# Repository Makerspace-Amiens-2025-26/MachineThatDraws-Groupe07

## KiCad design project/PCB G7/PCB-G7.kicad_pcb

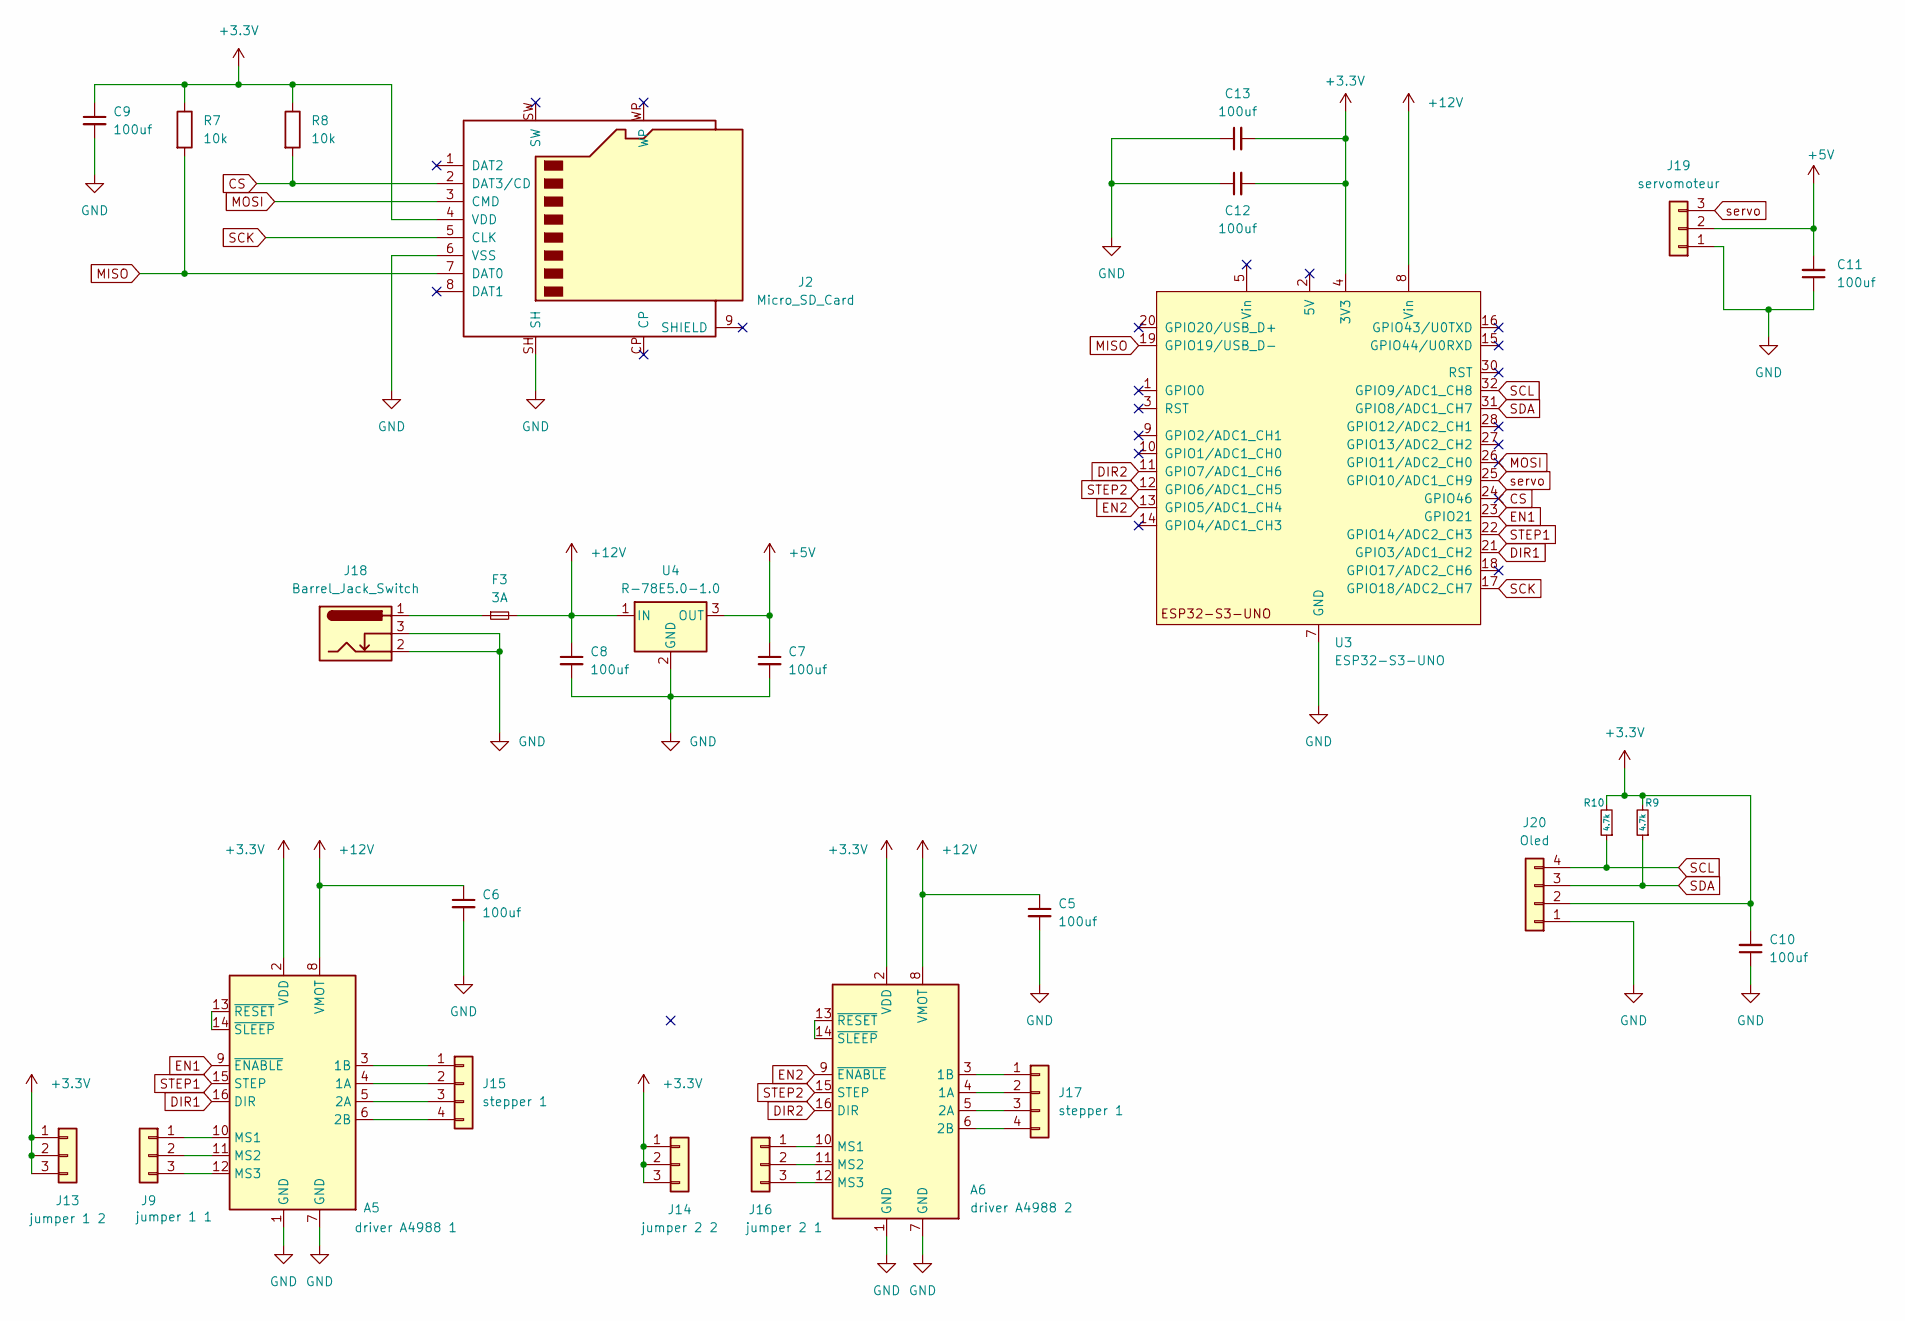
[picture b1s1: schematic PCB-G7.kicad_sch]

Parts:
A5: driver A4988 1; Pololu_Breakout-16_15.2x20.3mm
A6: driver A4988 2; Pololu_Breakout-16_15.2x20.3mm
C5, C6: 100uf; C_Radial_D8.0mm_H11.5mm_P3.50mm
C7, C8: 100uf; C_1206_3216Metric_Pad1.33x1.80mm_HandSolder
C9, C10, C12, C13: 100uf; C_1206
C11: 100uf; C_1206_3216Metric
F3: 3A; Fuseholder_Blade_Mini_Keystone_3568
J2: Micro_SD_Card; SD_Hirose_DM1AA_SF_PEJ82
J9: jumper 1 1; PinHeader_1x03_P2.54mm_Vertical
J13: jumper 1 2; PinHeader_1x03_P2.54mm_Vertical
J14: jumper 2 2; PinHeader_1x03_P2.54mm_Vertical
J15, J17: stepper 1; PinHeader_1x04_P2.54mm_Vertical
J16: jumper 2 1; PinHeader_1x03_P2.54mm_Vertical
J18: Barrel_Jack_Switch; BarrelJack_Horizontal
J19: servomoteur; PinHeader_1x03_P2.54mm_Vertical
J20: Oled; PinHeader_1x04_P2.54mm_Vertical
R7, R8: 10k; R_1206
R9, R10: 4.7k; R_1206
U3: ESP32-S3-UNO; ESP_S3_UNO
U4: R-78E5.0-1.0; Converter_DCDC_RECOM_R-78E-0.5_THT

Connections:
+3.3V: A5.2 (VDD), A6.2 (VDD), C9.1, C10.2, C12.2, C13.2, J2.4 (VDD), J13.1, J13.2, J13.3, J14.1, J14.2, J14.3, J20.2, R7.1, R8.1, R9.2, R10.2, U3.4 (3V3)
+5V: C7.1, C11.2, J19.2, U4.3 (OUT)
+12V: A5.8 (VMOT), A6.8 (VMOT), C5.1, C6.1, C8.1, F3.2, U3.8 (Vin), U4.1 (IN)
CS: J2.2 (DAT3/CD), R8.2, U3.24 (GPIO46)
DIR1: A5.16 (DIR), U3.21 (GPIO3/ADC1_CH2)
DIR2: A6.16 (DIR), U3.11 (GPIO7/ADC1_CH6)
EN1: A5.9 (~ENABLE), U3.23 (GPIO21)
EN2: A6.9 (~ENABLE), U3.13 (GPIO5/ADC1_CH4)
GND: A5.1 (GND), A5.7 (GND), A6.1 (GND), A6.7 (GND), C5.2, C6.2, C7.2, C8.2, C9.2, C10.1, C11.1, C12.1, C13.1, J2.6 (VSS), J2.SH, J18.2, J18.3, J19.1, J20.1, U3.6 (GND), U3.7 (GND), U3.29 (GND), U4.2 (GND)
MISO: J2.7 (DAT0), R7.2, U3.19 (GPIO19/USB_D-)
MOSI: J2.3 (CMD), U3.26 (GPIO11/ADC2_CH0)
unnamed: A5.4 (1A), J15.2
unnamed: A5.3 (1B), J15.1
unnamed: A5.5 (2A), J15.3
unnamed: A5.6 (2B), J15.4
unnamed: A5.10 (MS1), J9.1
unnamed: A5.11 (MS2), J9.2
unnamed: A5.12 (MS3), J9.3
unnamed: A5.13 (~RESET), A5.14 (~SLEEP)
unnamed: A6.4 (1A), J17.2
unnamed: A6.3 (1B), J17.1
unnamed: A6.5 (2A), J17.3
unnamed: A6.6 (2B), J17.4
unnamed: A6.10 (MS1), J16.1
unnamed: A6.11 (MS2), J16.2
unnamed: A6.12 (MS3), J16.3
unnamed: A6.13 (~RESET), A6.14 (~SLEEP)
unnamed: F3.1, J18.1
SCK: J2.5 (CLK), U3.17 (GPIO18/ADC2_CH7)
SCL: J20.4, R10.1, U3.32 (GPIO9/ADC1_CH8)
SDA: J20.3, R9.1, U3.31 (GPIO8/ADC1_CH7)
STEP1: A5.15 (STEP), U3.22 (GPIO14/ADC2_CH3)
STEP2: A6.15 (STEP), U3.12 (GPIO6/ADC1_CH5)
servo: J19.3, U3.25 (GPIO10/ADC1_CH9)

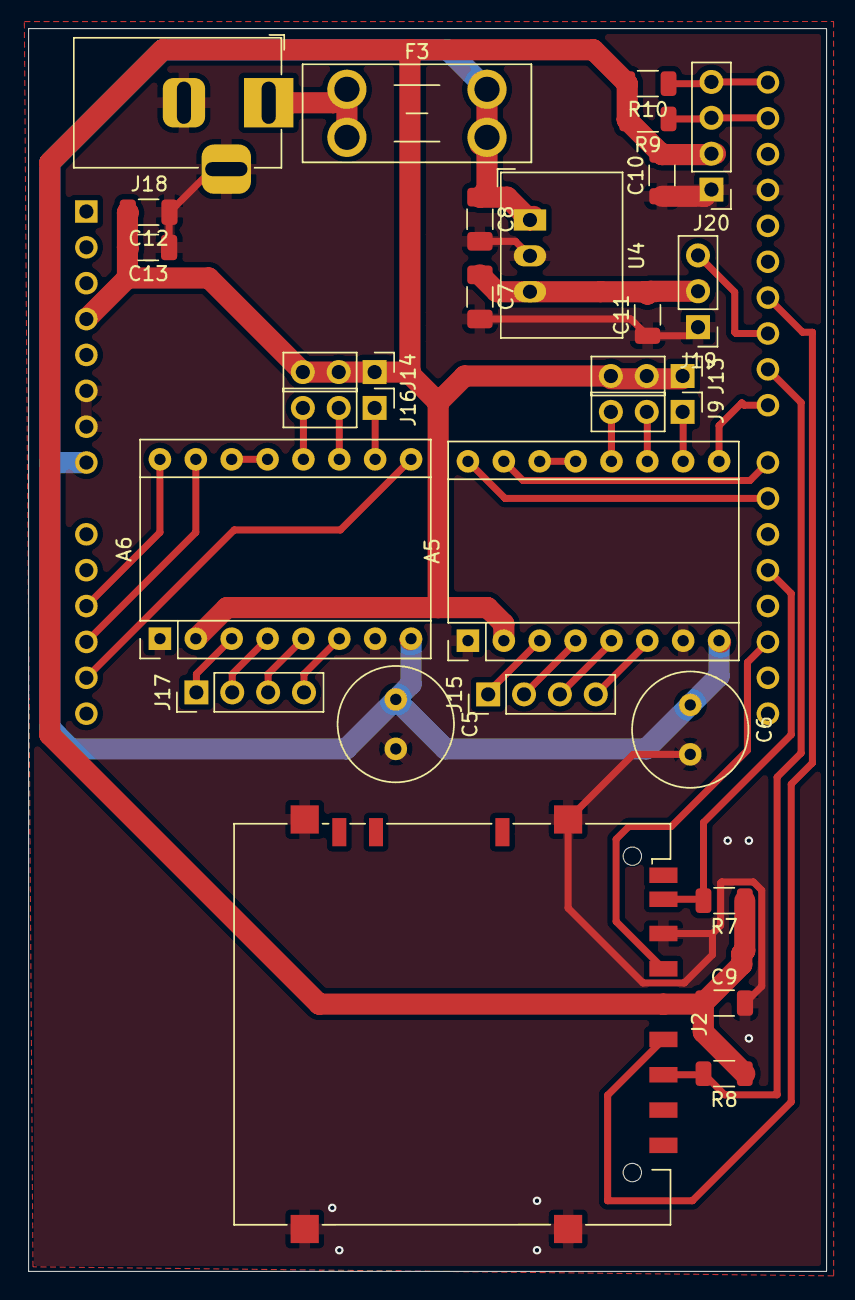
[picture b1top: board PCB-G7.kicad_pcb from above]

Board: 2 copper layers, 56.5 x 88.0 mm, 28 parts (0 on the bottom side), 34 nets.

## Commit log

2026-03-11 Revise documentation for DrawBot A4 project
    Updated the documentation for the DrawBot A4 project, enhancing project presentation, adding interactive 3D model and video sections, and improving navigation.
2026-03-11 Add custom CSS for animations and styling
2026-03-11 Add custom stylesheet to configuration
2026-03-11 Add PCB project documentation
    Document the PCB project objectives and steps.
2026-03-11 Revamp DrawBot A4 project page layout and content
    Updated the layout and content of the DrawBot A4 project page, including new styles and sections for better presentation.
2026-03-11 Refactor index.md layout and styles
2026-03-11 Add landing page layout in landing.html
2026-03-11 Update index.md with project details and media
2026-03-11 Revise documentation layout and content for DrawBot A4
    Updated the documentation for the DrawBot A4 project, including new sections and improved formatting.
2026-03-11 Revise PCB project documentation and specifications
    Updated the PCB project documentation to reflect new design objectives, specifications, and project steps.
2026-03-11 Revise PCB documentation for DrawBot A4 project
    Updated the PCB design documentation to reflect changes in project scope and component specifications.
2026-03-11 Revise PCB documentation for clarity and structure
2026-03-25 remplacement PCB
    J'ai déplacer les fichiers de la pcb dans le dossier projet, j'ai pu y apporter notament des modifications répondant aux demandes concernant le schematics , si je ne me trompe pas il manque un step d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
2026-03-25 update schematics
    mise à jour avec le schema actuel
2026-04-10 update schematics et pcb
2026-04-22 update pcb
2026-04-24 Validation PCB pour production
    Attention :
    - Plan de masse sur les deux couches
2026-04-27 fix some wiring problems
2026-06-06 Revamp documentation for DrawBot A4 project
    The documentation has been significantly expanded to include detailed sections on the DrawBot A4 project, including its mechanical, electronic, and software components, as well as assembly instructio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
2026-06-06 Restructure documentation for DrawBot A4 project
    The documentation has been restructured to provide a clearer overview of the DrawBot A4 project, including sections on the project introduction, workflow, and key resources. The HTML structure has be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
2026-06-06 Rename index.md to index_old.md
2026-06-06 Publishing custom app
2026-06-08 Replace pulley image with DrawBot poster image
